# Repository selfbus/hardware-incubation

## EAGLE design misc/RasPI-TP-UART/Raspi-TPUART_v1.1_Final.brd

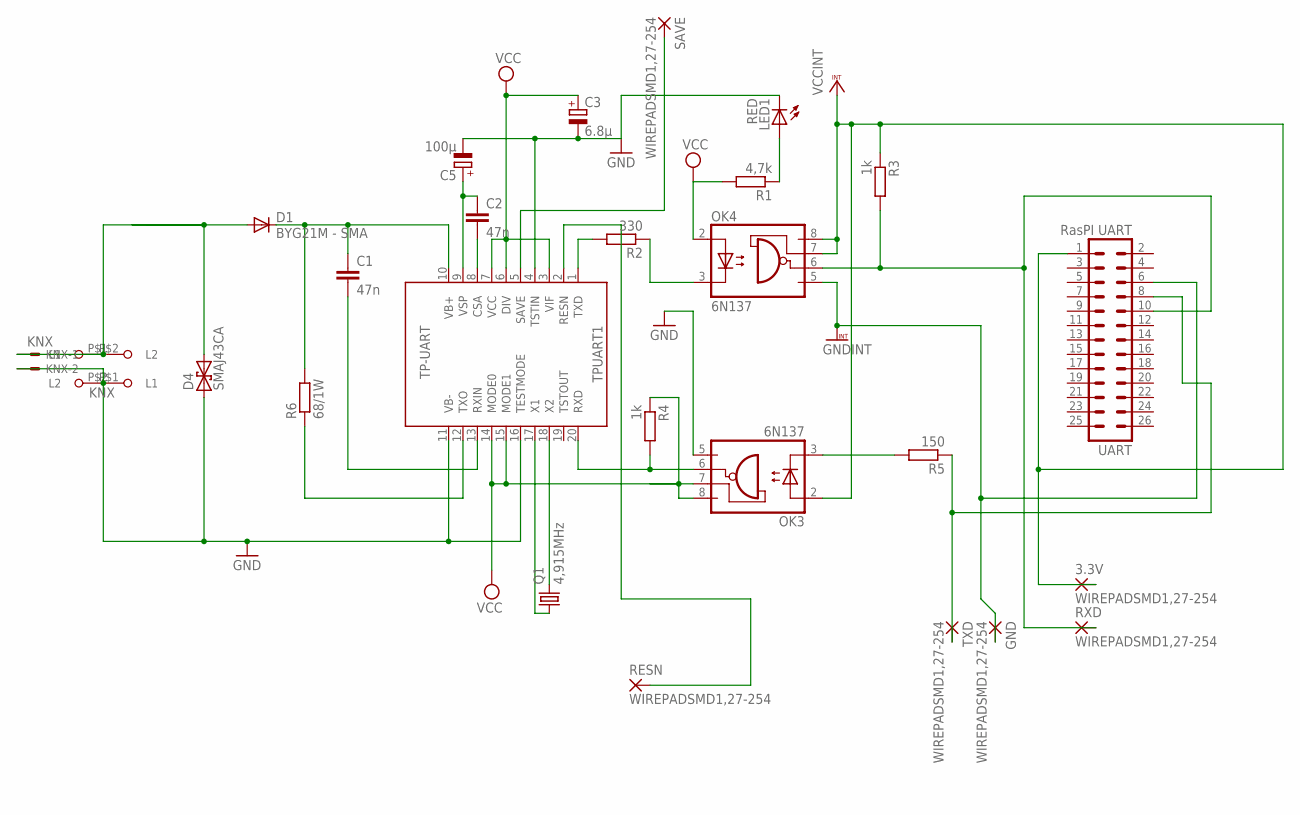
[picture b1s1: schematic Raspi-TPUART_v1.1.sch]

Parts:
3.3V: WIREPADSMD1,27-254; SMD1,27-2,54
C1, C2: 47n; C1206
C3: 6.8µ; CT7343
C5: 100µ; CT7343
D1: BYG21M - SMA; SMB
D4: SMAJ43CA; DO214AA
GND: WIREPADSMD1,27-254; SMD1,27-2,54
KNX: KNX; 22-23-2021
KNX_WAGO_243: 243-211
LED1: RED; KA-3528ASYC
OK3, OK4: 6N137; DIL8-SMD
Q1: 4,915MHz; HC49UP
R1: 4,7k; M1206
R2: 330; M1206
R3, R4: 1k; M1206
R5: 150; M1206
R6: 68/1W; R2512
RESN: WIREPADSMD1,27-254; SMD1,27-2,54
RXD: WIREPADSMD1,27-254; SMD1,27-2,54
SAVE: WIREPADSMD1,27-254; SMD1,27-2,54
TPUART1: TP-UART; SOIC20
TXD: WIREPADSMD1,27-254; SMD1,27-2,54
U$1: 243-211
UART: RasPI UART; MA13-2

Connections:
CSA: C2.2, TPUART1.8 (CSA)
GND: C3.-, C5.-, D4.A (1), KNX.2, KNX_WAGO_243.P$1 (L1), LED1.C, OK3.5 (GND), TPUART1.4 (TSTIN), TPUART1.11 (VB-), TPUART1.16 (TESTMODE), U$1.P$2 (L2)
GNDINT: GND.1, OK4.5 (GND), UART.6
KNX+: D1.A, D4.C (2), KNX.1, KNX_WAGO_243.P$2 (L2), U$1.P$1 (L1)
unnamed: OK3.3 (C), R5.2
unnamed: LED1.A, R1.1
RASPI_RXD: OK4.6 (VO), R3.2, RXD.1, UART.10
RASPI_TXD: R5.1, TXD.1, UART.8
RESN: RESN.1, TPUART1.2 (RESN)
RXD: OK3.6 (VO), R4.2, TPUART1.20 (RXD)
RXIN: C1.2, TPUART1.13 (RXIN)
SAVE: SAVE.1, TPUART1.5 (SAVE)
TXD: R2.2, TPUART1.1 (TXD)
TXD1: OK4.3 (C), R2.1
TXO: R6.1, TPUART1.12 (TXO)
VB+: C1.1, D1.C, R6.2, TPUART1.10 (VB+)
VCC: C3.+, OK3.7 (VE), OK3.8 (VCC), OK4.2 (A), R1.2, R4.1, TPUART1.3 (VIF), TPUART1.6 (DIV), TPUART1.7 (VCC), TPUART1.14 (MODE0), TPUART1.15 (MODE1)
VCCINT: 3.3V.1, OK3.2 (A), OK4.7 (VE), OK4.8 (VCC), R3.1, UART.1
VSP: C2.1, C5.+, TPUART1.9 (VSP)
X1: Q1.1, TPUART1.17 (X1)
X2: Q1.2, TPUART1.18 (X2)

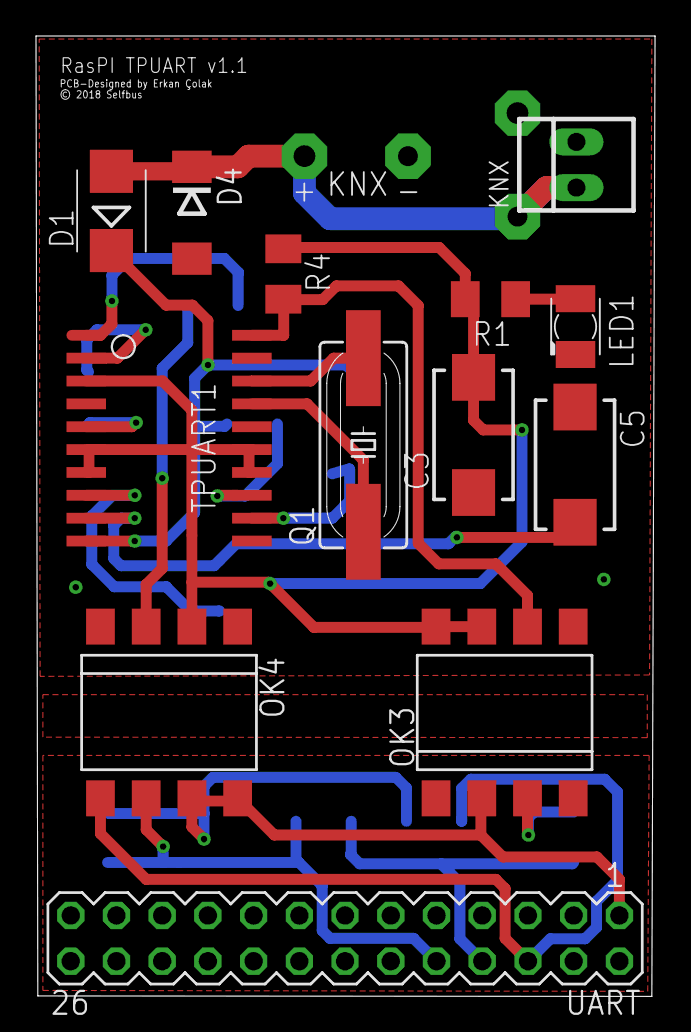
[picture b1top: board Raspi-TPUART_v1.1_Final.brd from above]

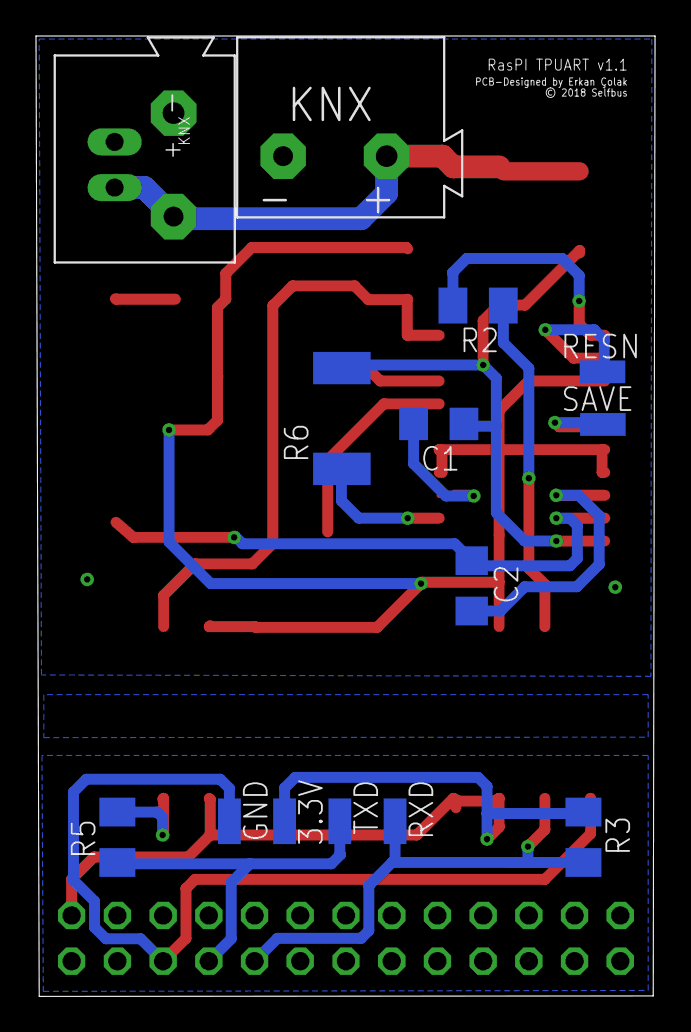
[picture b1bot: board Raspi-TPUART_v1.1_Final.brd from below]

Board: 2 copper layers, 34.4 x 53.4 mm, 27 parts (14 on the bottom side), 21 nets.

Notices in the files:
misc/RasPI-TP-UART/Raspi-TPUART_v1.1_Final.brd:
© 2018 Selfbus
